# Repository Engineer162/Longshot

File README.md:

# Longshot

## What This Project Is

Longshot is an open hardware and firmware project for designing and building a custom RF communication module.

This repository contains:
- EDA design files for the schematic and PCB layout
- Firmware sources for bring-up and control of the radio system
- Supporting documentation and licenses for development and release

Current version sends/recieves at 868MHz, but this can be changed in firmware, and by changing matching and lowpass filters in the schematic.

Why did i feel the need to create such a module from scratch? Because i simply wasnt satisfied by the speed & range that other modules like LoRa had, so i created my own.

## RF Main Components

| Function | IC / Module |
| --- | --- |
| Transceiver IC | SI4463 |
| PA / LNA | SKY66423-11 |

---

<sub>Note: I tried to use copilot AI to generate this repo structure as i have not tried that before. Safe to say i wont be attempting that in any future repo's. </sub>

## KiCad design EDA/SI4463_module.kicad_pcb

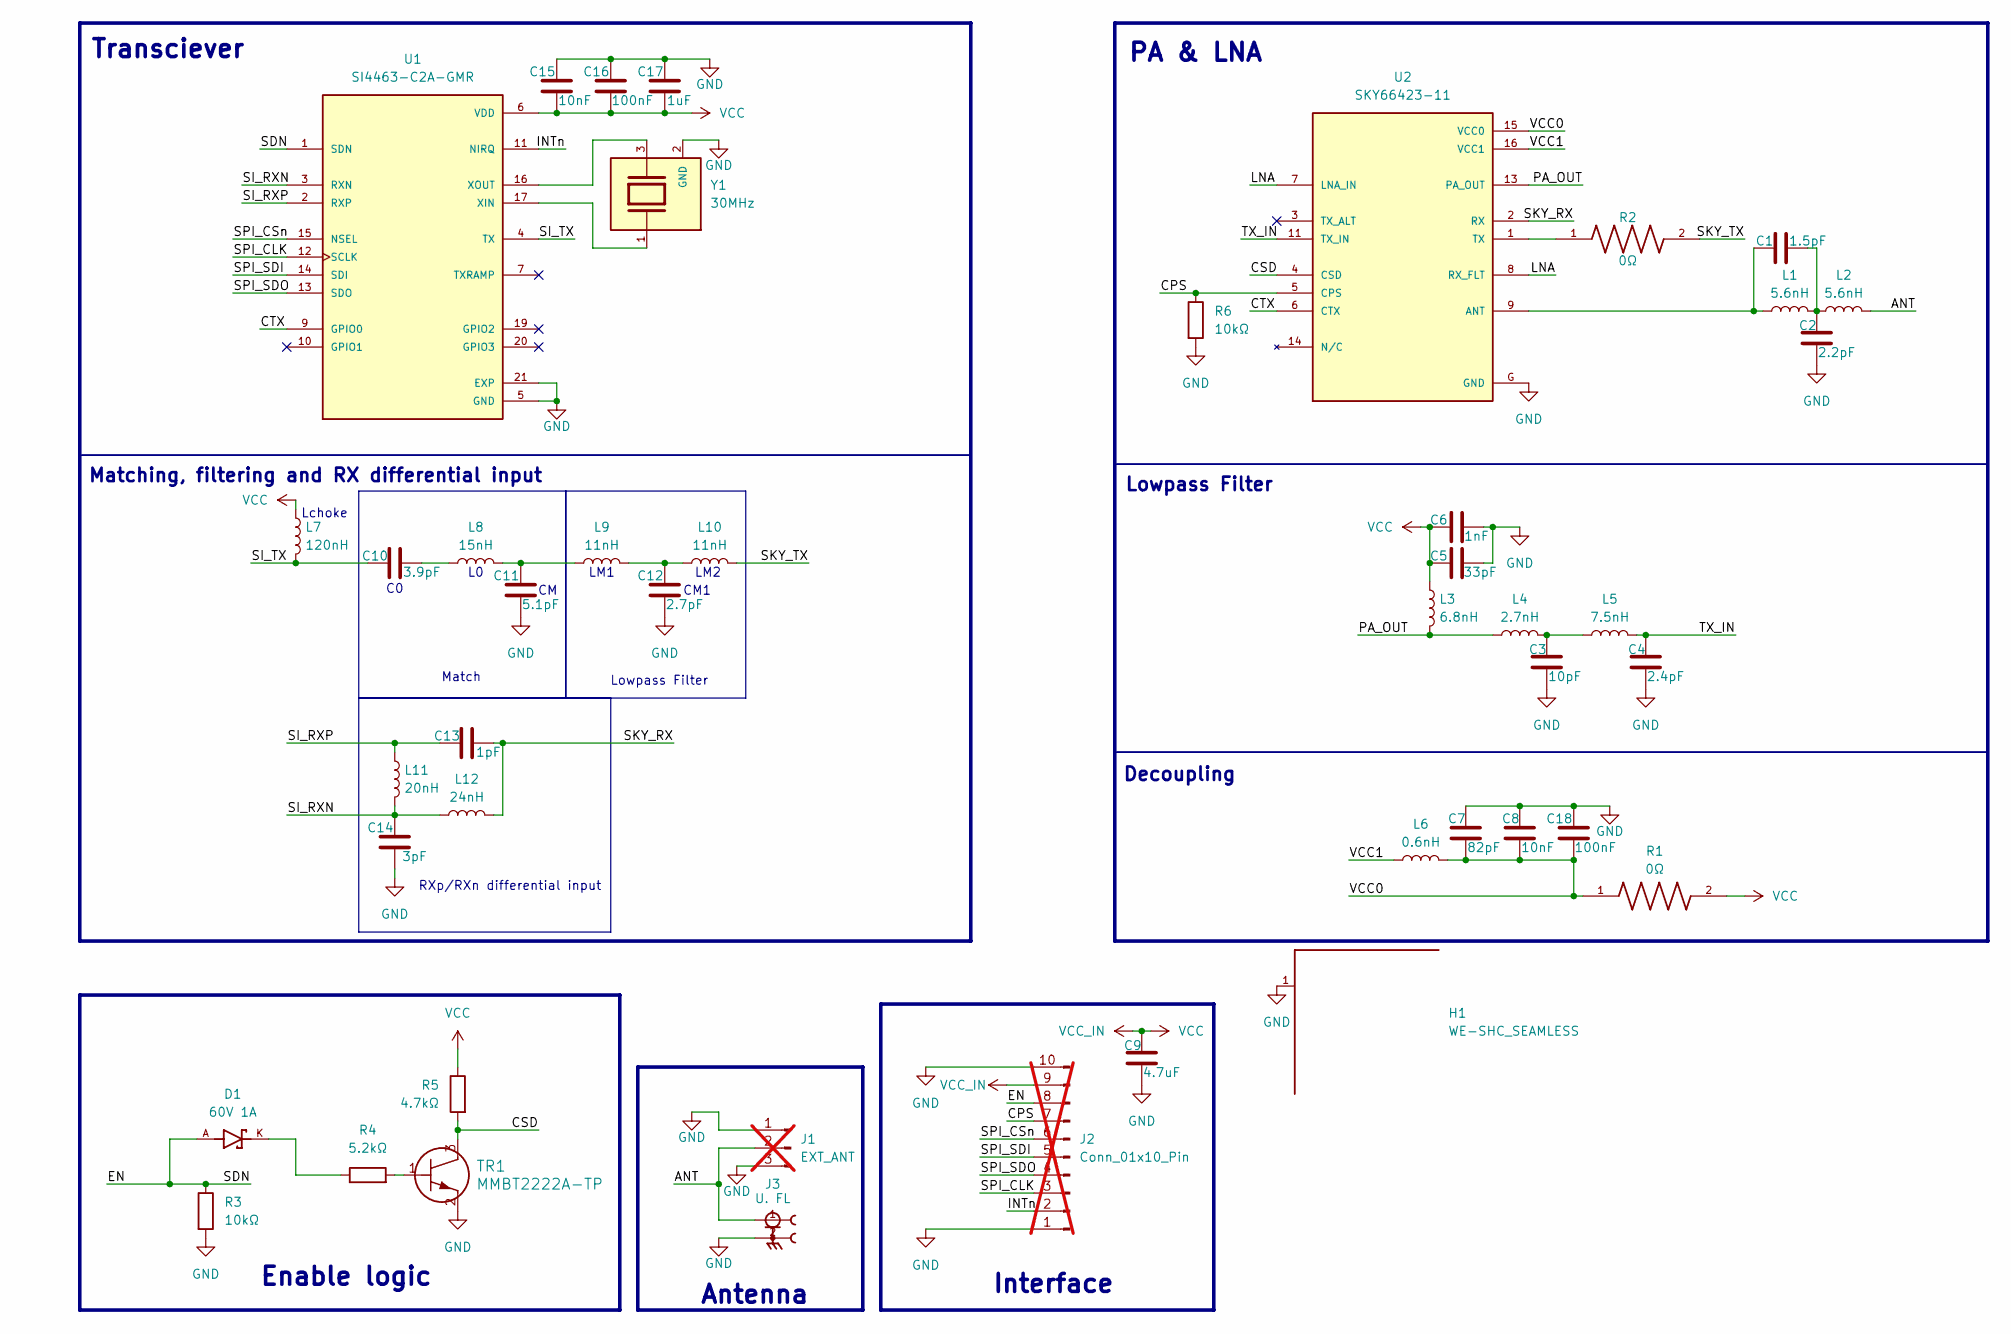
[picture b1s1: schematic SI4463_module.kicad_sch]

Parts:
C1: 1.5pF; C_0402_1005Metric
C2: 2.2pF; C_0402_1005Metric
C3: 10pF; C_0402_1005Metric
C4: 2.4pF; C_0402_1005Metric
C5: 33pF; C_0402_1005Metric
C6: 1nF; C_0402_1005Metric
C7: 82pF; C_0402_1005Metric
C8, C15: 10nF; C_0603_1608Metric
C9: 4.7uF; C_0603_1608Metric
C10: 3.9pF; C_0402_1005Metric
C11: 5.1pF; C_0402_1005Metric
C12: 2.7pF; C_0402_1005Metric
C13: 1pF; C_0402_1005Metric
C14: 3pF; C_0402_1005Metric
C16, C18: 100nF; C_1206_3216Metric
C17: 1uF; C_0603_1608Metric
D1: 60V 1A; DIO_MSS1P6-M3_89A; PARTREV 03-Aug-2020; DigiKey_Part_Number MSS1P6-M3/89AGICT-ND
H1: WE-SHC_SEAMLESS; WE-SHC_SEAMLESS_3670310; DigiKey_Part_Number 732-3670310-ND
J1: EXT_ANT; PinHeader_1x03_P2.00mm_Vertical; not fitted
J2: Conn_01x10_Pin; PinHeader_1x10_P2.00mm_Vertical; not fitted
J3: U. FL; LINX_CONUFL001-SMD-T; DigiKey_Part_Number CONUFL001-SMD-TCT-ND
L1, L2: 5.6nH; L_0402_1005Metric
L3: 6.8nH; L_0402_1005Metric
L4: 2.7nH; L_0402_1005Metric
L5: 7.5nH; L_0402_1005Metric
L6: 0.6nH; L_0201_0603Metric
L7: 120nH; L_0603_1608Metric
L8: 15nH; L_0402_1005Metric
L9, L10: 11nH; L_0201_0603Metric
L11: 20nH; L_0402_1005Metric
L12: 24nH; L_0805_2012Metric
R1, R2: 0Ω; RES_ERJ-2GE0R00X; PARTREV 3/1/2020; DigiKey_Part_Number P0.0JCT-ND
R3, R6: 10kΩ; R_0402_1005Metric
R4: 5.2kΩ; R_0805_2012Metric
R5: 4.7kΩ; R_0402_1005Metric
TR1: MMBT2222A-TP; MTR_MMBT2222A-TP_MCE
U1: SI4463-C2A-GMR; QFN50P400X400X90-21N; PARTREV 1.0; DigiKey_Part_Number 336-4346-1-ND
U2: SKY66423-11; XCVR_SKY66423-11; PARTREV June 9, 2023; DigiKey_Part_Number 863-2030-1-ND
Y1: 30MHz; XTAL_ABM8-30.000MHz-10-B1U-T; PARTREV 44041; DigiKey_Part_Number 535-14988-1-ND

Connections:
/ANT: J1.2, J3.1, L2.2
/CPS: J2.7, R6.1, U2.5 (CPS)
/CSD: R5.2, TR1.3, U2.4 (CSD)
/CTX: U1.9 (GPIO0), U2.6 (CTX)
/EN: D1.A, J2.8, R3.1, U1.1 (SDN)
/INTn: J2.2, U1.11 (NIRQ)
/LNA: U2.7 (LNA_IN), U2.8 (RX_FLT)
/PA_OUT: L3.2, L4.1, U2.13 (PA_OUT)
/SI_RXN: C14.2, L11.2, L12.1, U1.3 (RXN)
/SI_RXP: C13.1, L11.1, U1.2 (RXP)
/SI_TX: C10.1, L7.2, U1.4 (TX)
/SKY_RX: C13.2, L12.2, U2.2 (RX)
/SKY_TX: L10.2, R2.2
/SPI_CLK: J2.3, U1.12 (SCLK)
/SPI_CSn: J2.6, U1.15 (NSEL)
/SPI_SDI: J2.5, U1.14 (SDI)
/SPI_SDO: J2.4, U1.13 (SDO)
/TX_IN: C4.2, L5.2, U2.11 (TX_IN)
/VCC0: C7.1, C8.1, C18.1, L6.2, R1.1, U2.15 (VCC0)
/VCC1: L6.1, U2.16 (VCC1)
GND: C2.1, C3.1, C4.1, C5.2, C6.2, C7.2, C8.2, C9.1, C11.1, C12.1, C14.1, C15.2, C16.2, C17.2, C18.2, H1.1, H1.2, H1.3, H1.4, J1.1, J1.3, J2.1, J2.10, J3.2, J3.3, R3.2, R6.2, TR1.2, U1.5 (GND), U1.18 (GND), U1.21 (EXP), U2.G (GND), Y1.2 (GND), Y1.4 (GND)
unnamed: C1.2, C2.2, L1.2, L2.1
unnamed: C3.2, L4.2, L5.1
unnamed: C10.2, L8.1
unnamed: C11.2, L8.2, L9.1
unnamed: C12.2, L9.2, L10.1
unnamed: D1.K, R4.1
unnamed: R4.2, TR1.1
unnamed: U1.17 (XIN), Y1.1
unnamed: U1.16 (XOUT), Y1.3
unnamed: C1.1, L1.1, U2.9 (ANT)
unnamed: R2.1, U2.1 (TX)
VCC: C5.1, C6.1, C9.2, C15.1, C16.1, C17.1, J2.9, L3.1, L7.1, R1.2, R5.1, U1.6 (VDD), U1.8 (VDD)

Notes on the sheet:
PA & LNA
RXp/RXn differential input
CM1
Enable logic
Lowpass Filter
Lchoke
Transciever
LM1
LM2
Decoupling
Antenna
Matching, filtering and RX differential input
Match
Interface

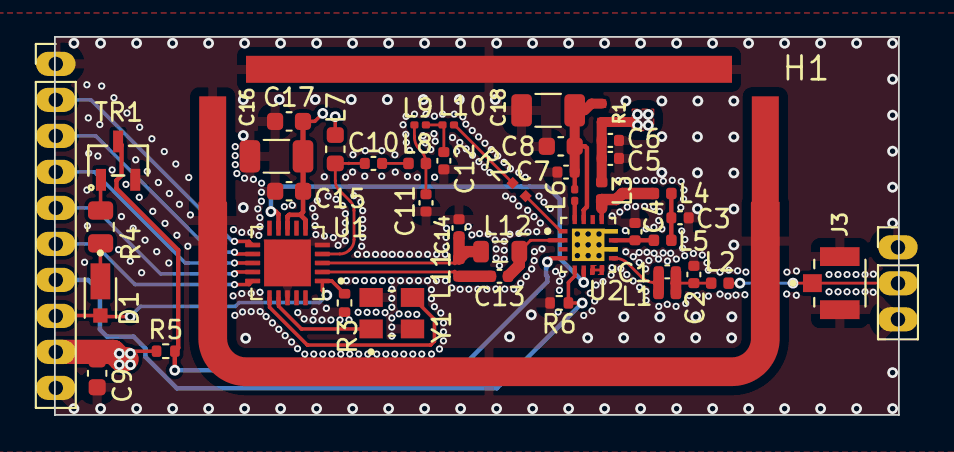
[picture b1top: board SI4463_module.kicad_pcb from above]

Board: 4 copper layers, 46.9 x 21.0 mm, 45 parts (0 on the bottom side), 33 nets.

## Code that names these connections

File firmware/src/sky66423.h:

/*
 * sky66423.h — Skyworks SKY66423-11 front-end module (FEM) driver.
 *
 * The SKY66423-11 integrates a power amplifier (PA), a low-noise amplifier
 * (LNA), and a T/R switch into a single package. It operates from
 * 169 MHz to 960 MHz and is controlled by three digital GPIO lines:
 *
 *   CSD — Chip Shutdown (active high = enabled, low = off)
 *   CTX — TX/RX select  (high = TX mode, low = RX mode)
 *   CPS — Bypass mode   (high = bypass PA/LNA, low = normal)
 *
 * In a Longshot system the CTX pin is driven directly by the SI4463 GPIO0
 * configured as TX_STATE, so the FEM automatically follows the radio state.
 * CSD and CPS are driven by the host MCU.
 */

#ifndef SKY66423_H
#define SKY66423_H

#include <stdint.h>

#ifdef __cplusplus
extern "C" {
#endif

/* -------------------------------------------------------------------------
 * Return codes
 * ---------------------------------------------------------------------- */
typedef enum {
    SKY66423_OK        =  0,
    SKY66423_ERR_PARAM = -1,
} sky66423_err_t;

/* -------------------------------------------------------------------------
 * Hardware abstraction layer
 * ---------------------------------------------------------------------- */
typedef struct {
    /* Drive the CSD (chip shutdown) pin: 1 = enabled, 0 = shutdown */
    void (*csd_write)(int level);

    /* Drive the CPS (bypass) pin: 1 = bypass mode, 0 = normal mode */
    void (*cps_write)(int level);

    /*
     * Optional: drive the CTX pin explicitly.
     * If NULL the CTX pin is assumed to be wired directly to the SI4463
     * GPIO0 (TX_STATE) and is managed automatically by the radio hardware.
     */
    void (*ctx_write)(int level);

    /* Delay in microseconds (used for mode-transition settling). */
    void (*delay_us)(uint32_t us);
} sky66423_hal_t;

/* -------------------------------------------------------------------------
 * Operating modes
 * ---------------------------------------------------------------------- */
typedef enum {
    SKY66423_MODE_SHUTDOWN = 0, /* Full shutdown, minimum current        */
    SKY66423_MODE_RX,           /* RX mode (LNA active, T/R in RX path)  */
    SKY66423_MODE_TX,           /* TX mode (PA active, T/R in TX path)   */
    SKY66423_MODE_BYPASS,       /* Bypass PA and LNA (test/calibration)  */
} sky66423_mode_t;

/* -------------------------------------------------------------------------
 * Driver handle
 * ---------------------------------------------------------------------- */
typedef struct {
    sky66423_hal_t  hal;
    sky66423_mode_t mode;
} sky66423_t;

/* -------------------------------------------------------------------------
 * API
 * ---------------------------------------------------------------------- */

/*
 * sky66423_init — Initialise the driver handle and assert shutdown.
 *
 * Call this before any other sky66423_* function. The FEM will be held in
 * shutdown until sky66423_set_mode() is called.
 */
sky66423_err_t sky66423_init(sky66423_t *dev, const sky66423_hal_t *hal);

/*
 * sky66423_set_mode — Set the operating mode of the SKY66423-11.
 *
 * Mode transitions complete within ~3 µs (typical). The function inserts a
 * short settling delay after changing mode.
 */
sky66423_err_t sky66423_set_mode(sky66423_t *dev, sky66423_mode_t mode);

/*
 * sky66423_get_mode — Return the current operating mode.
 */
sky66423_mode_t sky66423_get_mode(const sky66423_t *dev);

/*
 * sky66423_shutdown — Convenience wrapper to assert full shutdown.
 */
static inline sky66423_err_t sky66423_shutdown(sky66423_t *dev)
{
    return sky66423_set_mode(dev, SKY66423_MODE_SHUTDOWN);
}

/*
 * sky66423_enable_rx — Convenience wrapper to switch to RX mode.
 */
static inline sky66423_err_t sky66423_enable_rx(sky66423_t *dev)
{
    return sky66423_set_mode(dev, SKY66423_MODE_RX);
}

/*
 * sky66423_enable_tx — Convenience wrapper to switch to TX mode.
 *
 * Note: When CTX is wired to the SI4463 GPIO0 (TX_STATE), the hardware
 * automatically manages TX/RX switching. Calling this function is only
 * necessary when CTX is controlled by the MCU (hal.ctx_write != NULL).
 */
static inline sky66423_err_t sky66423_enable_tx(sky66423_t *dev)
{
    return sky66423_set_mode(dev, SKY66423_MODE_TX);
}

#ifdef __cplusplus
}
#endif

#endif /* SKY66423_H */

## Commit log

2026-04-02 Initial plan
2026-04-02 Add firmware source files (SI4463 + SKY66423-11 drivers)
    Agent-Logs-Url: https://github.com/Engineer162/Longshot/sessions/9d958f46-317f-44e2-a4f9-6c4d20e2f5a9
2026-04-02 Pushed schematic progress
2026-04-02 Clarify motivation for custom RF module development
    Explain the motivation behind developing a custom RF module due to dissatisfaction with existing options.
2026-04-03 Added edge headers, and assigned MPN's and footprints.
2026-04-03 Made PCB, placed components, routed almost all of them (missing power traces). added EMI shield.
2026-04-04 Finished PCB
2026-04-04 Forgot to add stitching on RX differential input section.
2026-04-04 added 2 missing traces
